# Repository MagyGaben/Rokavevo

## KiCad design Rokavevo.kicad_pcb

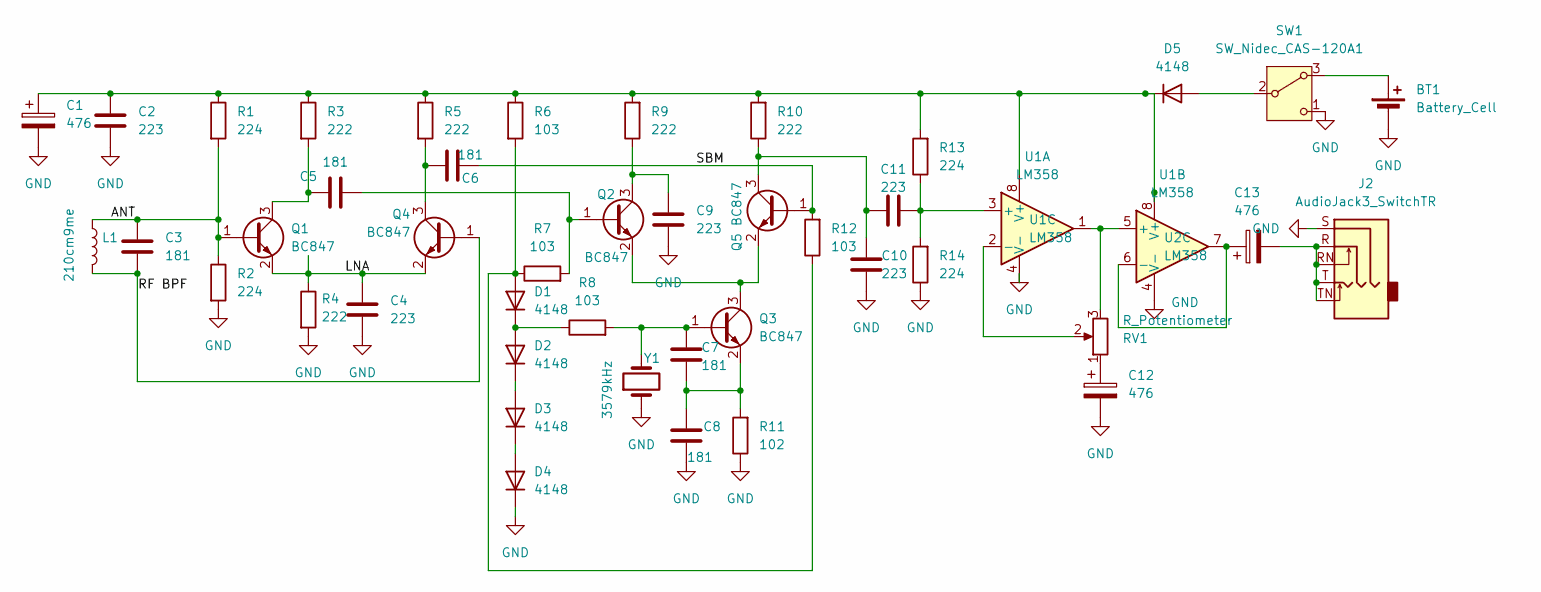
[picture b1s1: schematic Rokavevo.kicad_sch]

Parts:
BT1: Battery_Cell; PinSocket_1x02_P2.54mm_Vertical
C1, C12, C13: 476; CP_Elec_6.3x5.3
C2, C4, C9, C10, C11: 223; C_0805_2012Metric_Pad1.18x1.45mm_HandSolder
C3, C5, C6, C7, C8: 181; C_1206_3216Metric_Pad1.33x1.80mm_HandSolder
D1, D2, D3, D4: 4148; D_0805_2012Metric_Pad1.15x1.40mm_HandSolder
D5: 4148; D_SMB-SMC_Universal_Handsoldering
J2: AudioJack3_SwitchTR; Jack_3.5mm_CUI_SJ1-3515N_Horizontal
L1: 210cm9me; PinHeader_1x02_P2.54mm_Vertical
Q1, Q2, Q3, Q4, Q5: BC847; SOT-23
R1, R2, R13, R14: 224; R_1206_3216Metric_Pad1.30x1.75mm_HandSolder
R3, R4, R5, R9, R10: 222; R_1206_3216Metric_Pad1.30x1.75mm_HandSolder
R6, R7, R8, R12: 103; R_1206_3216Metric_Pad1.30x1.75mm_HandSolder
R11: 102; R_1206_3216Metric_Pad1.30x1.75mm_HandSolder
RV1: R_Potentiometer; Potentiometer_Omeg_PC16BU_Vertical
SW1: SW_Nidec_CAS-120A1; SW_Toggle_Blue_wSlots
U1: LM358; SOIC-8_3.9x4.9mm_P1.27mm
U2: LM358
Y1: 3579kHz; Crystal_HC49-4H_Vertical

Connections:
/ANT: C3.1, L1.1, Q1.1 (B), R1.2, R2.1
/LNA: C4.1, Q1.2 (E), Q4.2 (E), R4.1
/RF BPF: C3.2, L1.2, Q4.1 (B)
/SBM: C6.2, Q5.1 (B), R12.2
GND: BT1.2 (-), C1.2, C2.2, C4.2, C8.1, C9.1, C10.1, C12.2, D4.1 (K), J2.S, R2.2, R4.2, R11.1, R14.1, SW1.1 (C), U1.4 (V-), U2.4 (V-), Y1.1
unnamed: BT1.1 (+), SW1.3 (A)
unnamed: C12.1, RV1.1
unnamed: C13.2, J2.R, J2.RN, J2.T, J2.TN
unnamed: D1.2 (A), R6.2, R7.1, R12.1
unnamed: D1.1 (K), D2.2 (A), R8.1
unnamed: D2.1 (K), D3.2 (A)
unnamed: D3.1 (K), D4.2 (A)
unnamed: D5.2 (A), SW1.2 (B)
unnamed: C1.1, C2.1, D5.1 (K), R1.1, R3.1, R5.1, R6.1, R9.2, R10.2, R13.2, U1.8 (V+), U2.8 (V+)
unnamed: C5.2, Q1.3 (C), R3.2
unnamed: C5.1, Q2.1 (B), R7.2
unnamed: C9.2, Q2.3 (C), R9.1
unnamed: Q2.2 (E), Q3.3 (C), Q5.2 (E)
unnamed: C7.2, Q3.1 (B), R8.2, Y1.2
unnamed: C7.1, C8.2, Q3.2 (E), R11.2
unnamed: C6.1, Q4.3 (C), R5.2
unnamed: C10.2, C11.2, Q5.3 (C), R10.1
unnamed: C11.1, R13.1, R14.2, U1.3 (+)
unnamed: RV1.2, U1.2 (-)
unnamed: RV1.3, U1.1, U1.5 (+)
unnamed: C13.1, U1.6 (-), U1.7

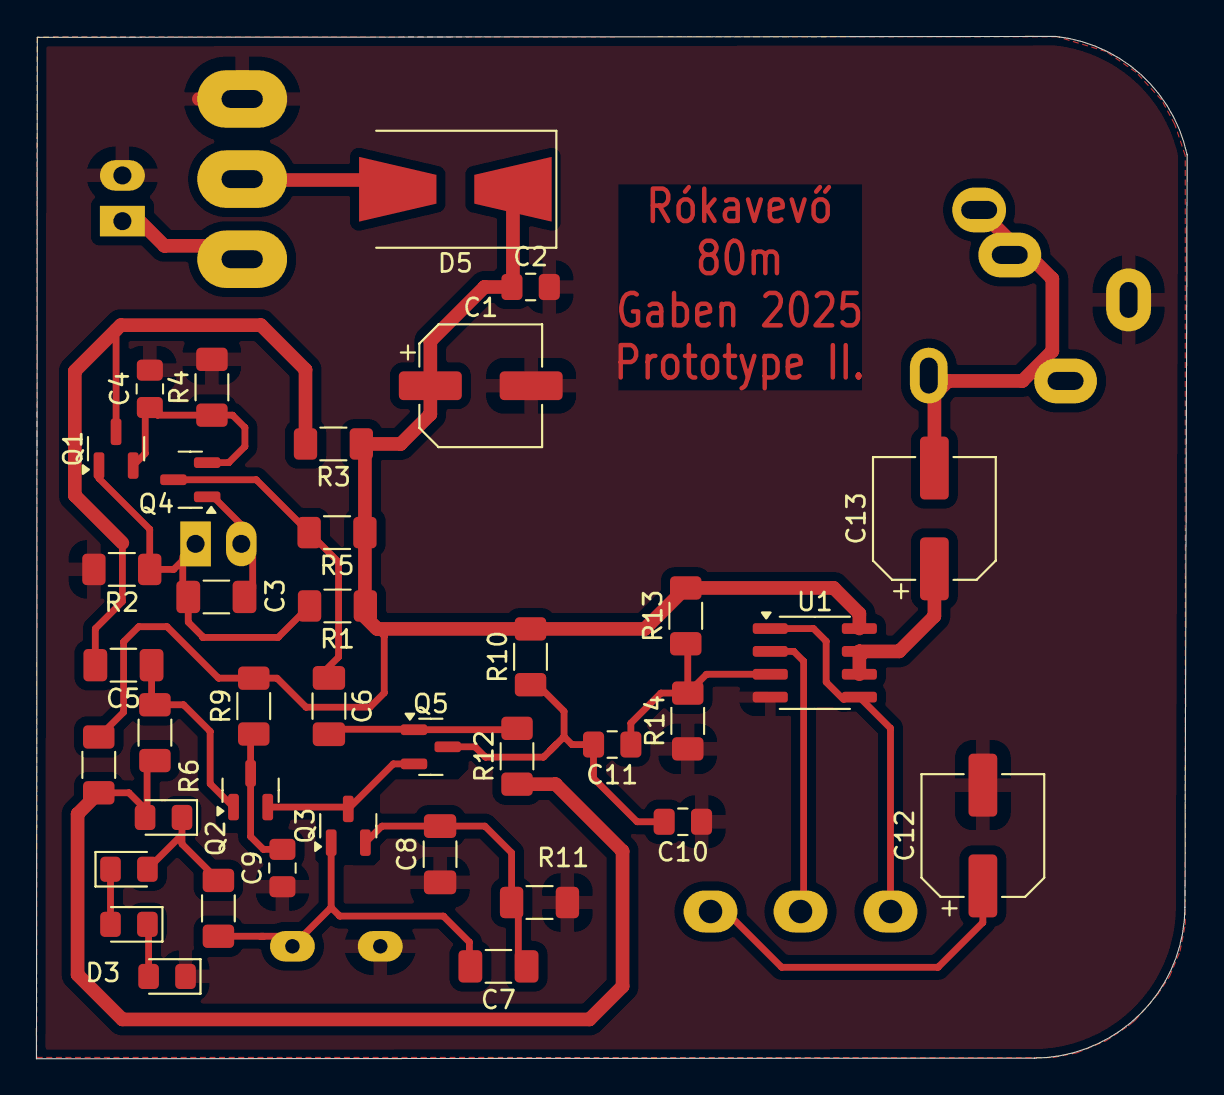
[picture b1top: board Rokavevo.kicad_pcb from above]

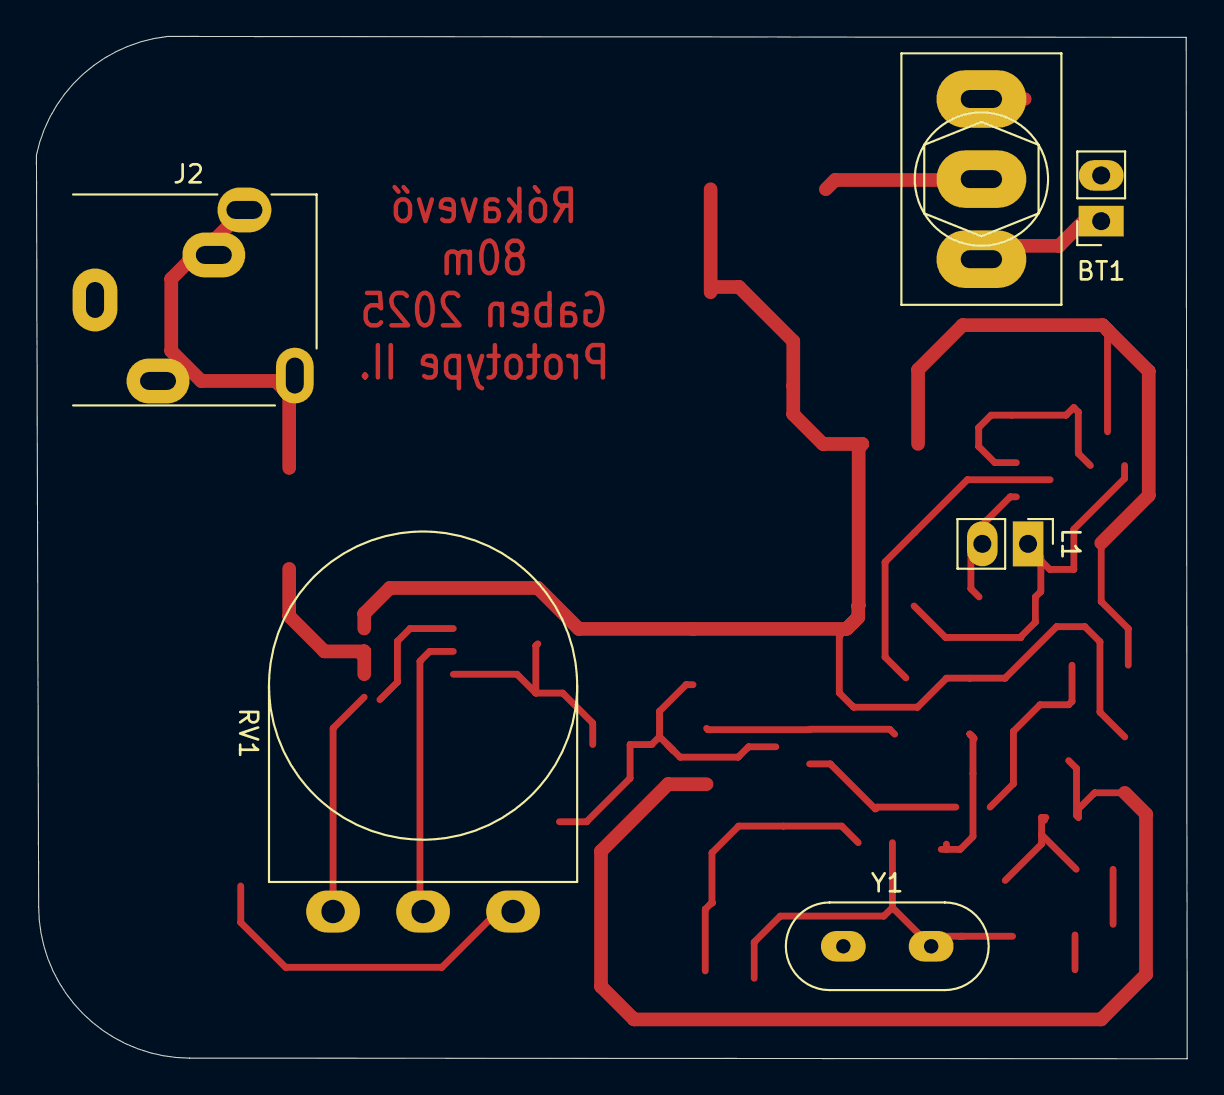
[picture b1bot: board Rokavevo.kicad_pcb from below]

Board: 2 copper layers, 63.9 x 56.8 mm, 44 parts (6 on the bottom side), 26 nets.

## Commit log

2025-06-13 Initial comit
2025-07-02 Prototype II
    Fixed schematic, new pcb design, Printable mask
